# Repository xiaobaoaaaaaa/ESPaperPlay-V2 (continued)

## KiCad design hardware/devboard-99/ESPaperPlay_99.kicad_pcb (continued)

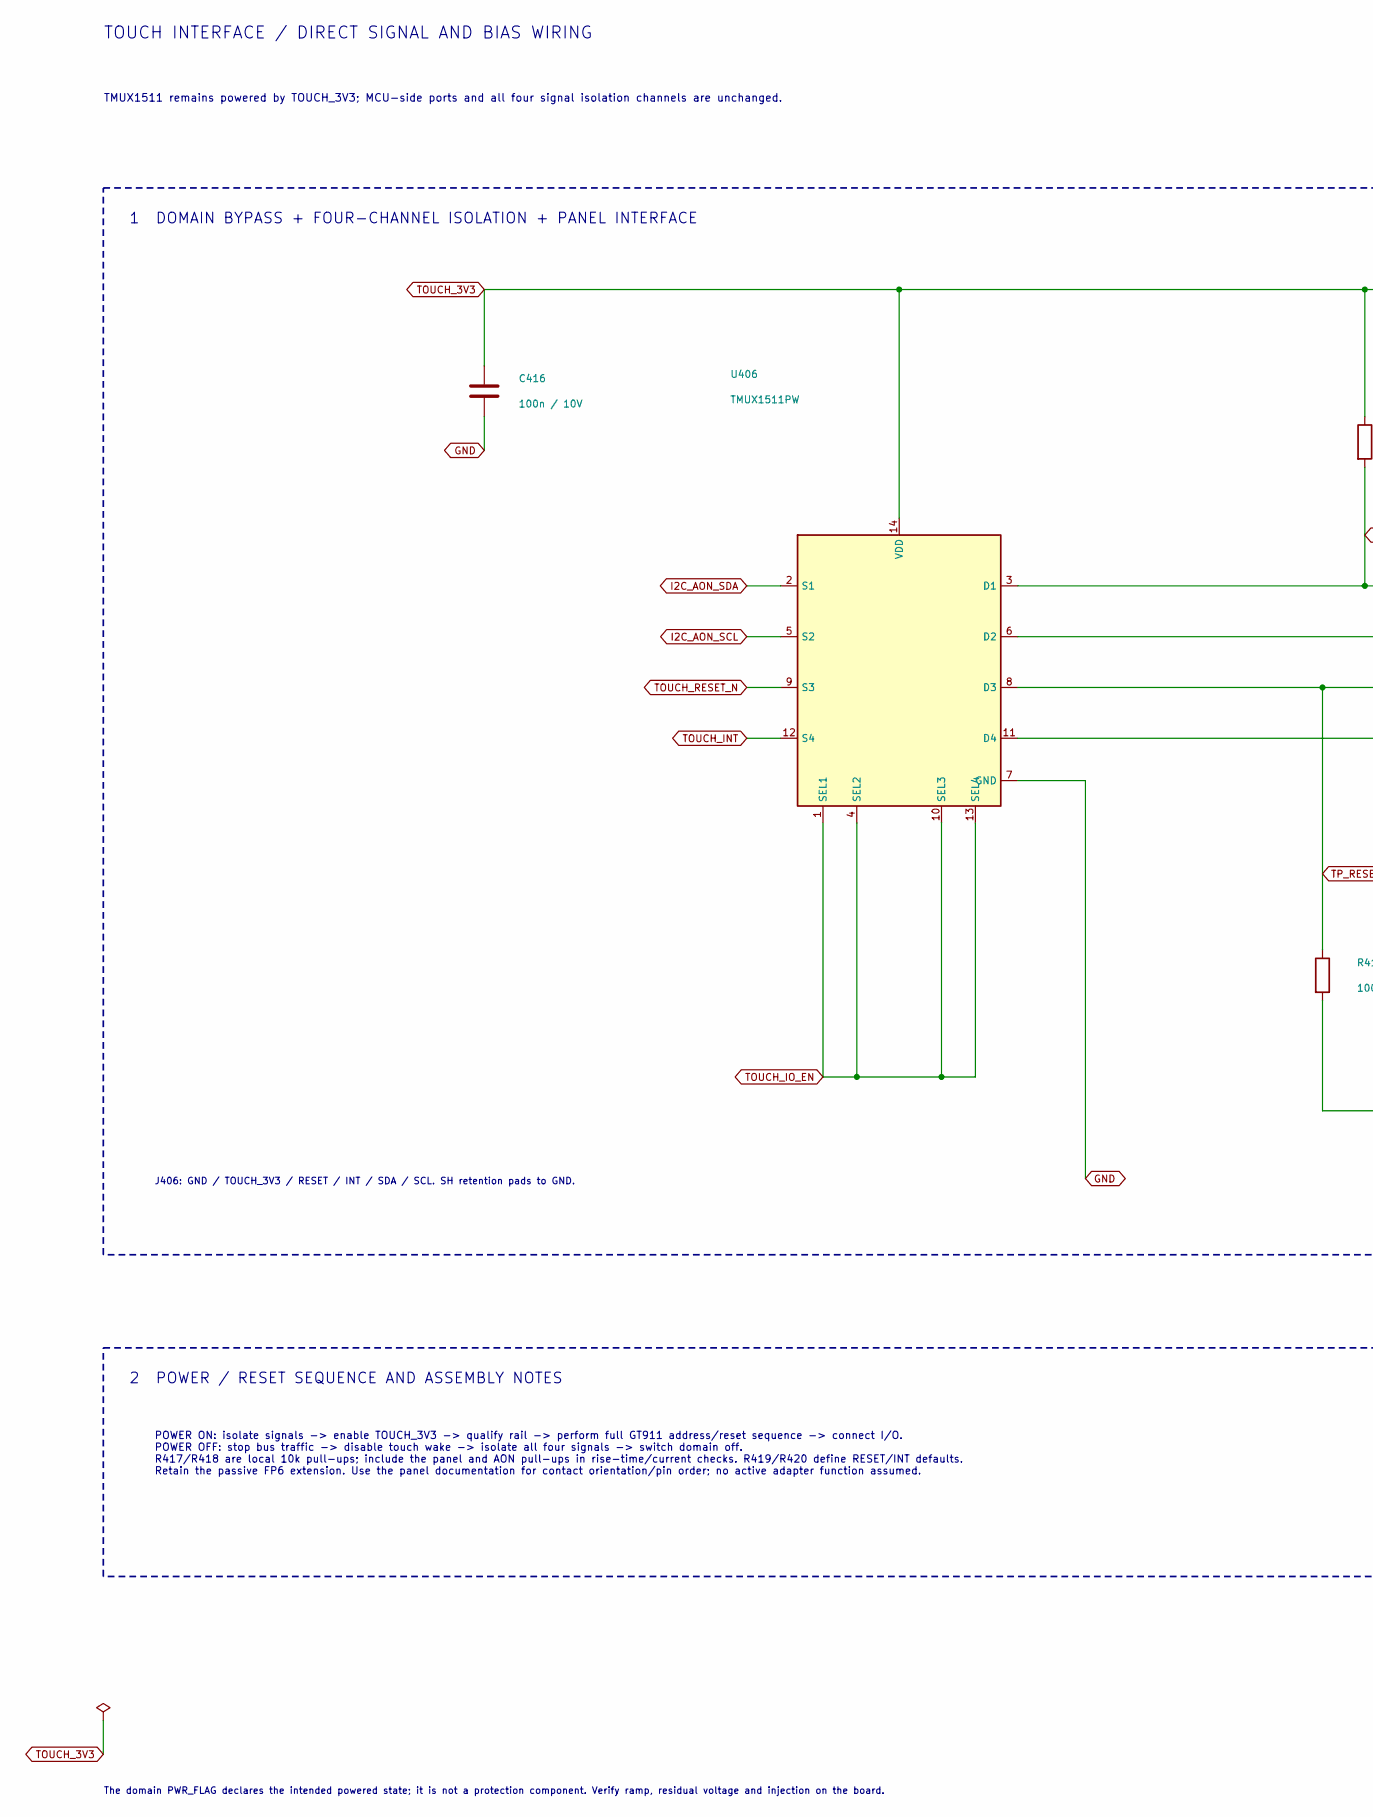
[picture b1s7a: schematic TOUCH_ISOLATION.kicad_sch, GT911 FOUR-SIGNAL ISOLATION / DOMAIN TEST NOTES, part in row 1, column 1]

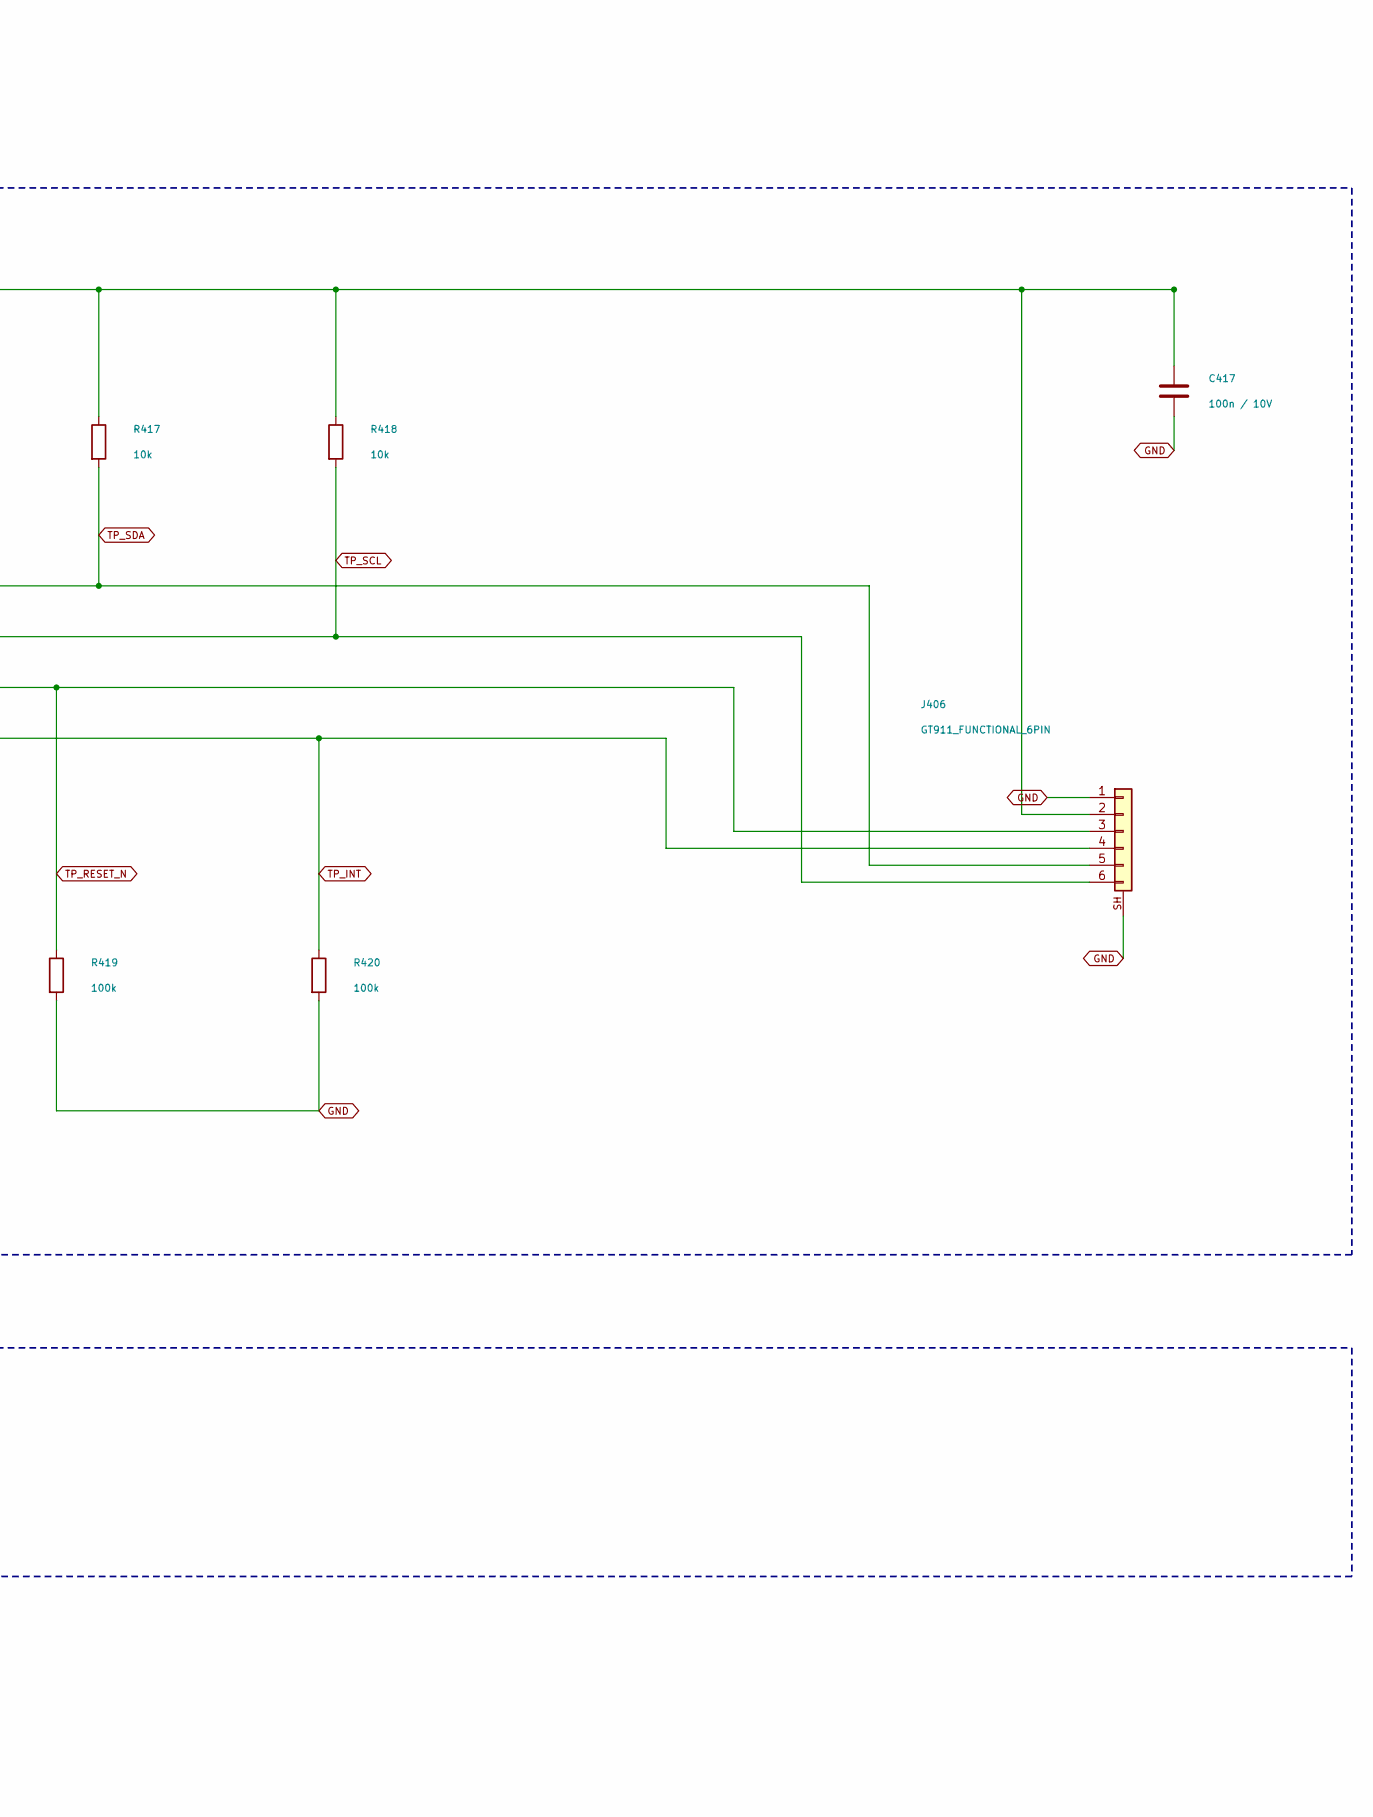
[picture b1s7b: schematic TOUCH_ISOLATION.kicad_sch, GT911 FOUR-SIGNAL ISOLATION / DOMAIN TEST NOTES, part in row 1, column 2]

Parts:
C416, C417: 100n / 10V; C_0603_1608Metric
J406: GT911_FUNCTIONAL_6PIN; LAILAN_LAIL-FPC-CDX01-6P0.5-GW_1x06_P0.50mm_SH
R417, R418: 10k; R_0603_1608Metric
R419, R420: 100k; R_0603_1608Metric
U406: TMUX1511PW; TSSOP-14_4.4x5mm_P0.65mm

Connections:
GND: C416.2, C417.2, J406.1, J406.SH, R419.2, R420.2, U406.7 (GND); also elsewhere on the board
I2C_AON_SCL: U406.5 (S2); also elsewhere on the board
I2C_AON_SDA: U406.2 (S1); also elsewhere on the board
TOUCH_3V3: C416.1, C417.1, J406.2, R417.1, R418.1, U406.14 (VDD); also elsewhere on the board
TOUCH_INT: U406.12 (S4); also elsewhere on the board
TOUCH_IO_EN: U406.1 (SEL1), U406.4 (SEL2), U406.10 (SEL3), U406.13 (SEL4); also elsewhere on the board
TOUCH_RESET_N: U406.9 (S3); also elsewhere on the board
TP_INT: J406.4, R420.1, U406.11 (D4)
TP_RESET_N: J406.3, R419.1, U406.8 (D3)
TP_SCL: J406.6, R418.2, U406.6 (D2)
TP_SDA: J406.5, R417.2, U406.3 (D1)

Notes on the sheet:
TOUCH INTERFACE / DIRECT SIGNAL AND BIAS WIRING
TMUX1511 remains powered by TOUCH_3V3; MCU-side ports and all four signal isolation channels are unchanged.
1 DOMAIN BYPASS + FOUR-CHANNEL ISOLATION + PANEL INTERFACE
J406: GND / TOUCH_3V3 / RESET / INT / SDA / SCL. SH retention pads to GND.
2 POWER / RESET SEQUENCE AND ASSEMBLY NOTES
POWER ON: isolate signals -> enable TOUCH_3V3 -> qualify rail -> perform full GT911 address/reset sequence -> connect I/O. POWER OFF: stop bus traffic -> disable touch wake -> isolate all four signals -> switch domain off. R417/R418 are local 10k pull-ups; include the panel and AON pull-ups in rise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
The domain PWR_FLAG declares the intended powered state; it is not a protection component. Verify ramp, residual voltage and injection on the board.

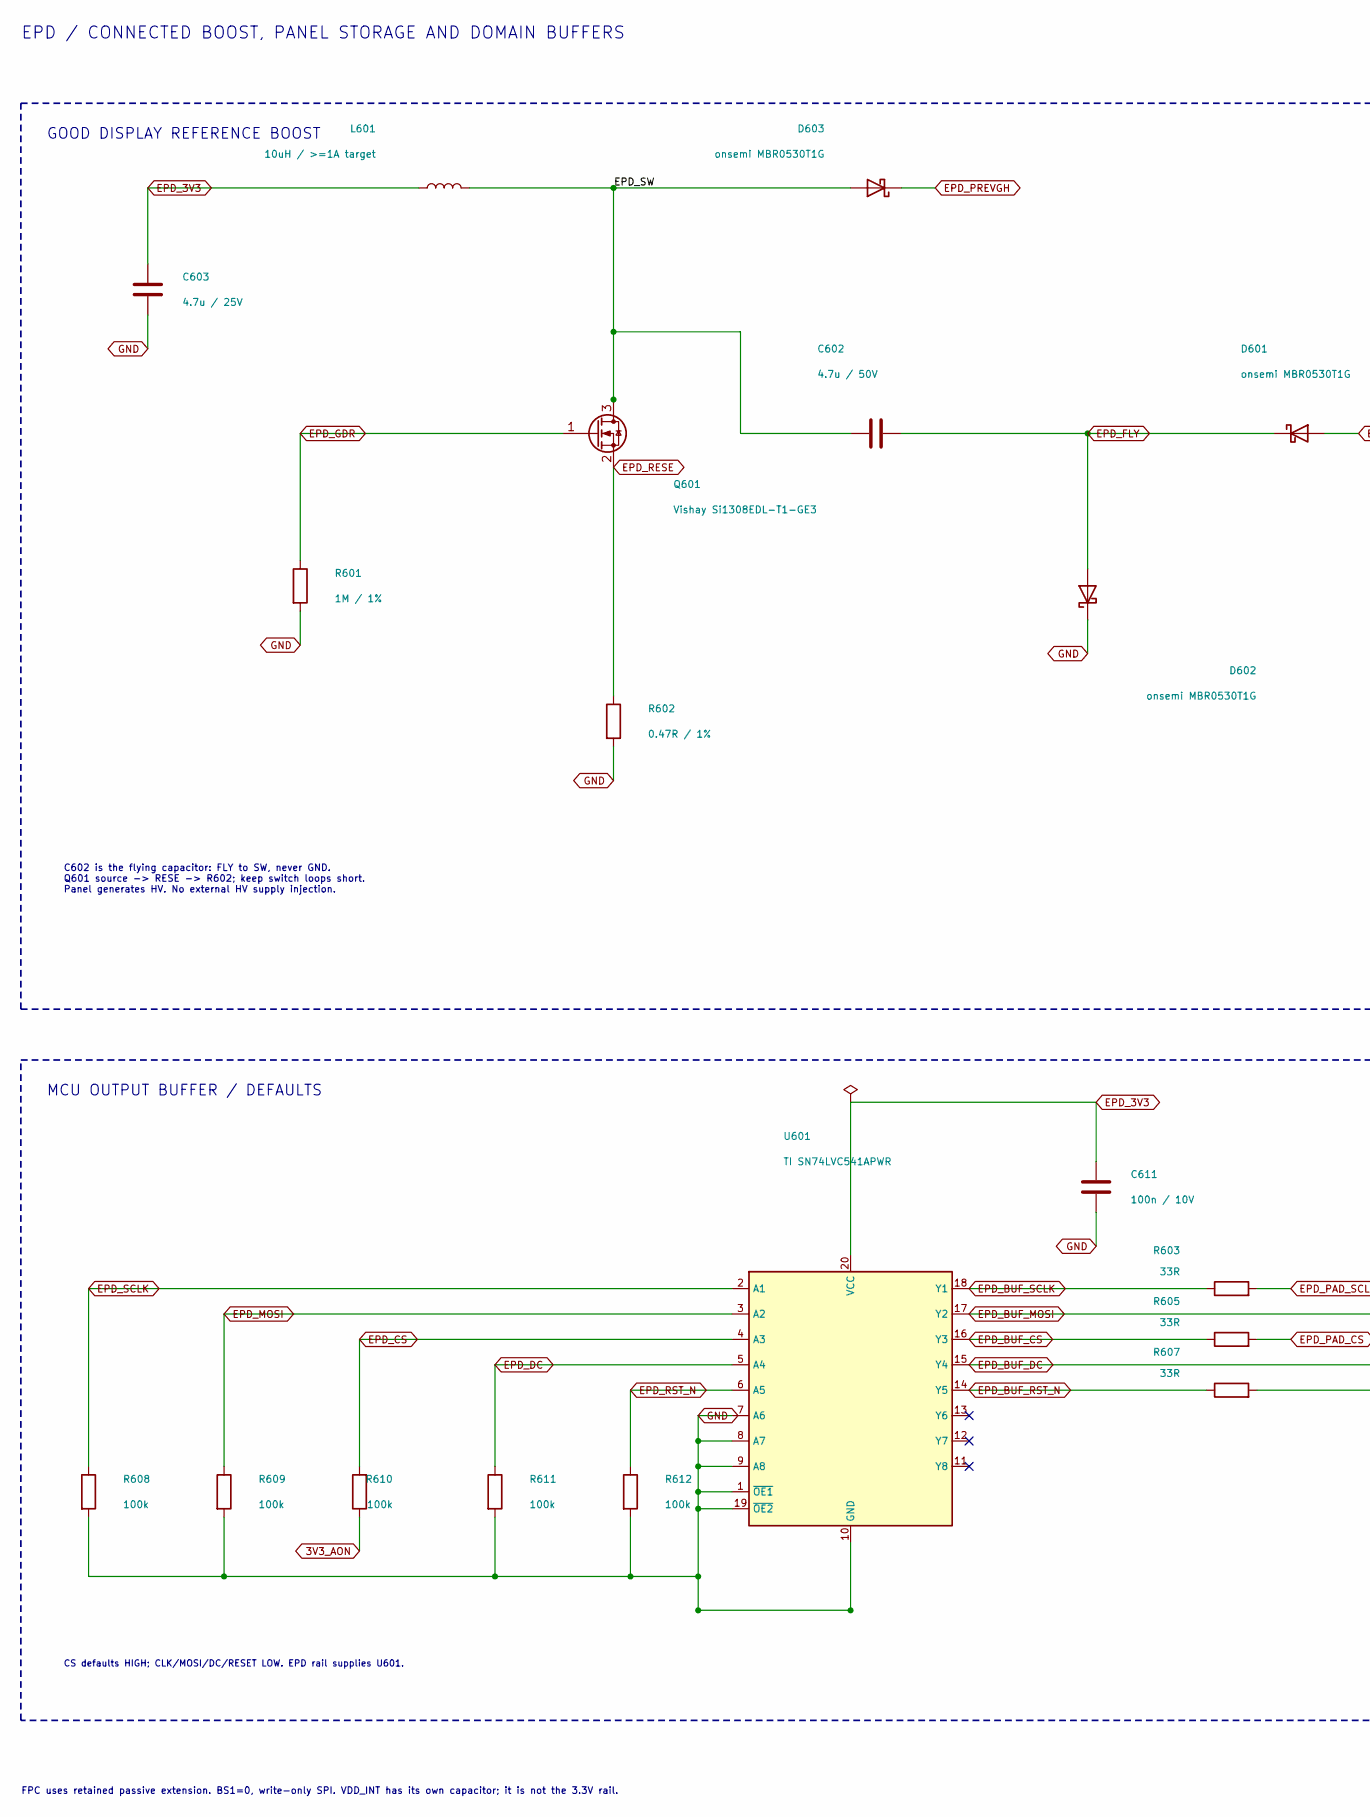
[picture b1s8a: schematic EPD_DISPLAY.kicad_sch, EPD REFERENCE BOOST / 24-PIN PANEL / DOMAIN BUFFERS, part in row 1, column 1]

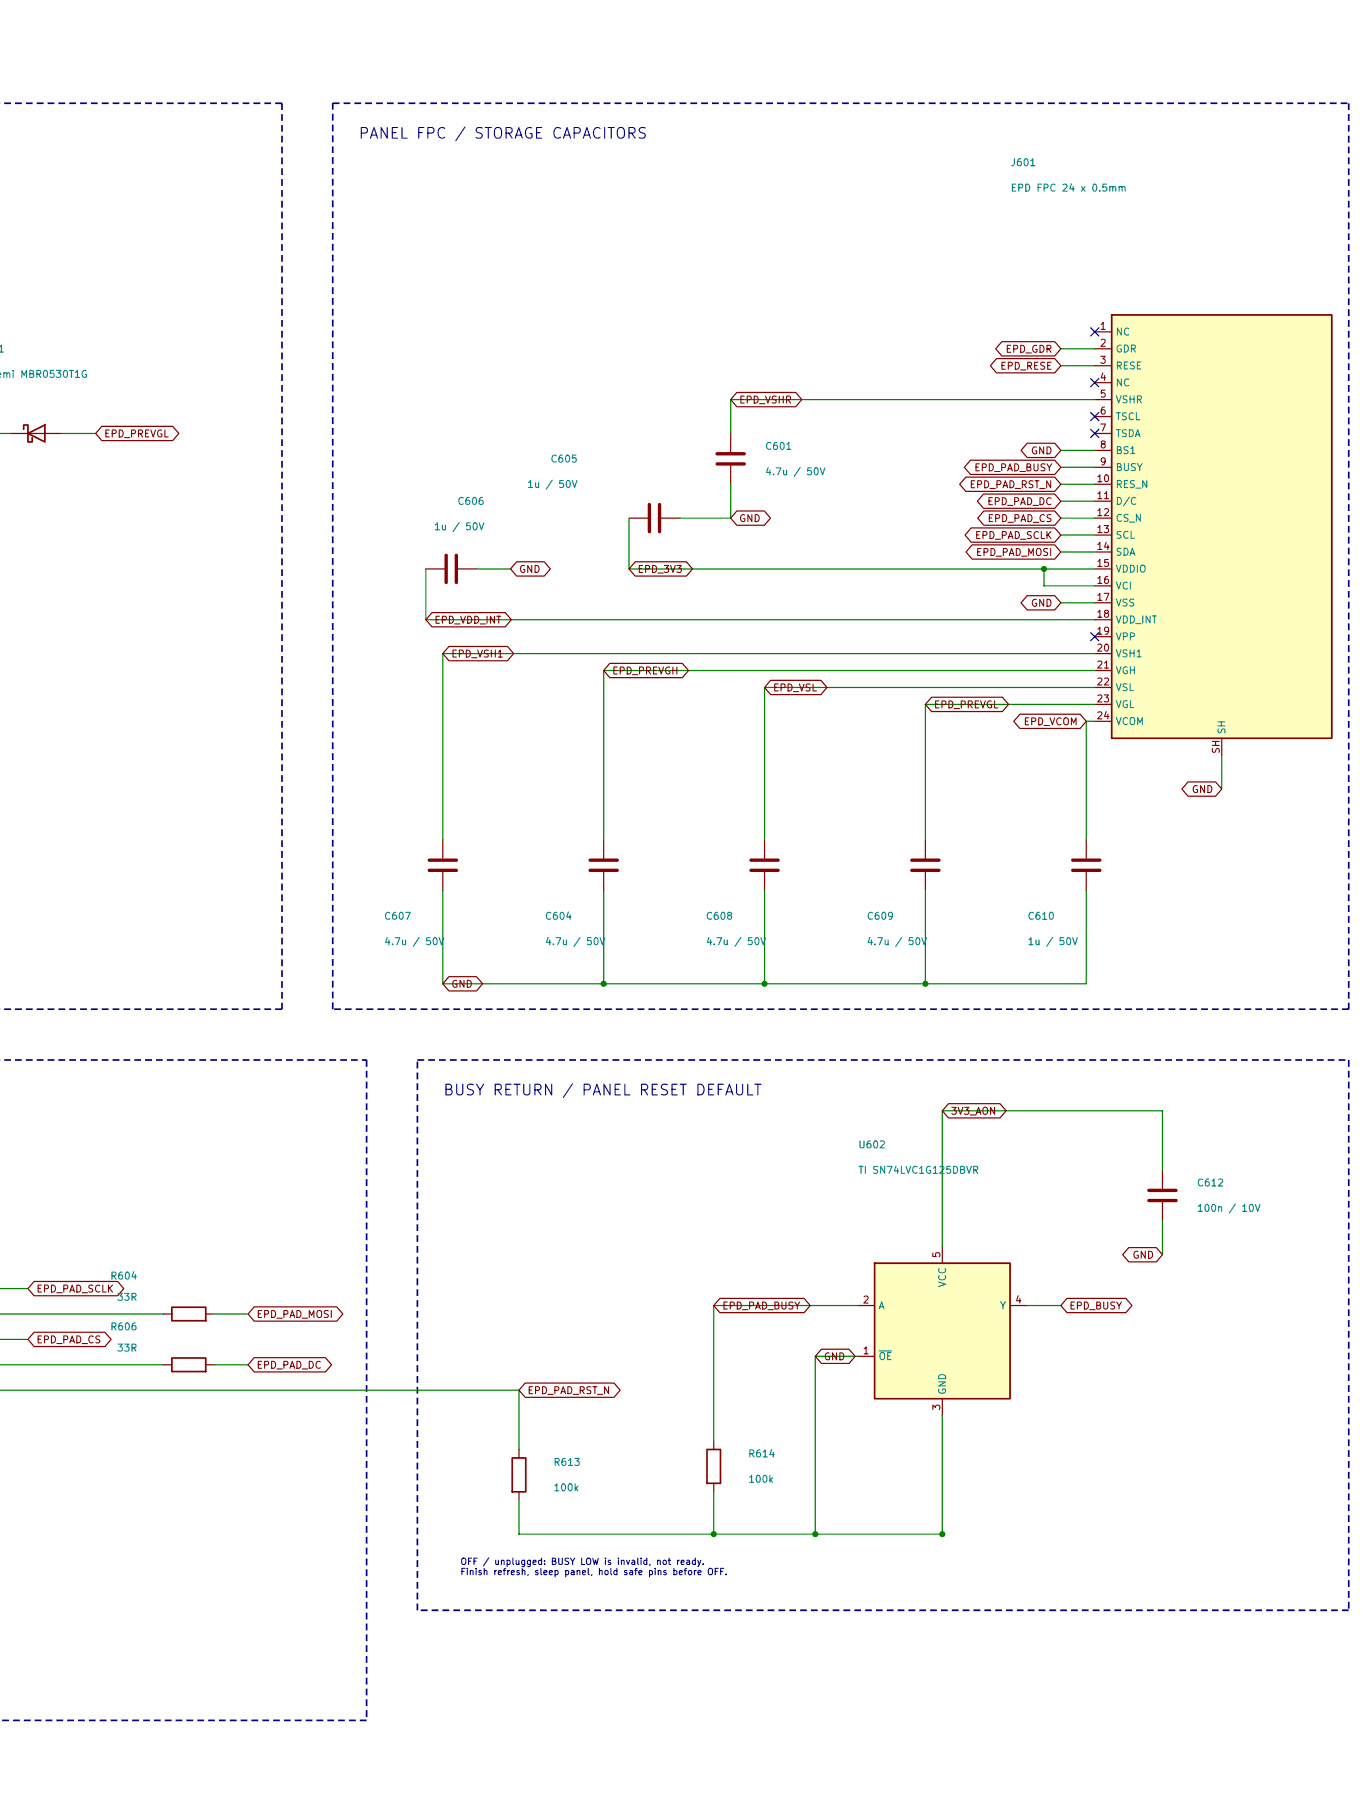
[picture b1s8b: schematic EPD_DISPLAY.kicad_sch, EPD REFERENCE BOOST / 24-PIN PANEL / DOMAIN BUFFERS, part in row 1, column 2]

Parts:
C601, C602, C604, C607, C608, C609: 4.7u / 50V; C_1206_3216Metric
C603: 4.7u / 25V; C_0805_2012Metric
C605, C606, C610: 1u / 50V; C_0805_2012Metric
C611, C612: 100n / 10V; C_0603_1608Metric
D601, D602, D603: onsemi MBR0530T1G; D_SOD-123
J601: EPD FPC 24 x 0.5mm; HOAUC_HYCW3D-05FPC24-200B_1x24_P0.50mm_SH
L601: 10uH / >=1A target; L_Bourns-SRN4018
Q601: Vishay Si1308EDL-T1-GE3; Vishay_SC70_3_AN826_72601
R601: 1M / 1%; R_0603_1608Metric
R602: 0.47R / 1%; Vishay_WFM2010_5.08x2.54mm
R603, R604, R605, R606, R607: 33R; R_0603_1608Metric
R608, R609, R610, R611, R612, R613, R614: 100k; R_0603_1608Metric
U601: TI SN74LVC541APWR; TSSOP-20_4.4x6.5mm_P0.65mm
U602: TI SN74LVC1G125DBVR; SOT-23-5

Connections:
3V3_AON: C612.1, R610.1, U602.5 (VCC); also elsewhere on the board
/EPD_DISPLAY/EPD_SW: C602.2, D603.2 (A), L601.2, Q601.3 (D)
EPD_3V3: C603.1, C605.1, C611.1, J601.15 (VDDIO), J601.16 (VCI), L601.1, U601.20 (VCC); also elsewhere on the board
EPD_BUF_CS: R605.1, U601.16 (Y3)
EPD_BUF_DC: R606.1, U601.15 (Y4)
EPD_BUF_MOSI: R604.1, U601.17 (Y2)
EPD_BUF_RST_N: R607.1, U601.14 (Y5)
EPD_BUF_SCLK: R603.1, U601.18 (Y1)
EPD_BUSY: U602.4 (Y); also elsewhere on the board
EPD_CS: R610.2, U601.4 (A3); also elsewhere on the board
EPD_DC: R611.1, U601.5 (A4); also elsewhere on the board
EPD_FLY: C602.1, D601.1 (K), D602.2 (A)
EPD_GDR: J601.2 (GDR), Q601.1 (G), R601.1
EPD_MOSI: R609.1, U601.3 (A2); also elsewhere on the board
EPD_PAD_BUSY: J601.9 (BUSY), R614.1, U602.2 (A)
EPD_PAD_CS: J601.12 (CS_N), R605.2
EPD_PAD_DC: J601.11 (D/C), R606.2
EPD_PAD_MOSI: J601.14 (SDA), R604.2
EPD_PAD_RST_N: J601.10 (RES_N), R607.2, R613.1
EPD_PAD_SCLK: J601.13 (SCL), R603.2
EPD_PREVGH: C604.1, D603.1 (K), J601.21 (VGH)
EPD_PREVGL: C609.1, D601.2 (A), J601.23 (VGL)
EPD_RESE: J601.3 (RESE), Q601.2 (S), R602.1
EPD_RST_N: R612.1, U601.6 (A5); also elsewhere on the board
EPD_SCLK: R608.1, U601.2 (A1); also elsewhere on the board
EPD_VCOM: C610.1, J601.24 (VCOM)
EPD_VDD_INT: C606.1, J601.18 (VDD_INT)
EPD_VSH1: C607.1, J601.20 (VSH1)
EPD_VSHR: C601.1, J601.5 (VSHR)
EPD_VSL: C608.1, J601.22 (VSL)
GND: C601.2, C603.2, C604.2, C605.2, C606.2, C607.2, C608.2, C609.2, C610.2, C611.2, C612.2, D602.1 (K), J601.8 (BS1), J601.17 (VSS), J601.SH, R601.2, R602.2, R608.2, R609.2, R611.2, R612.2, R613.2, R614.2, U601.1 (~OE1), U601.7 (A6), U601.8 (A7), U601.9 (A8), U601.10 (GND), U601.19 (~OE2), U602.1 (~OE), U602.3 (GND); also elsewhere on the board

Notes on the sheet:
EPD / CONNECTED BOOST, PANEL STORAGE AND DOMAIN BUFFERS
GOOD DISPLAY REFERENCE BOOST
PANEL FPC / STORAGE CAPACITORS
MCU OUTPUT BUFFER / DEFAULTS
BUSY RETURN / PANEL RESET DEFAULT
C602 is the flying capacitor: FLY to SW, never GND. Q601 source -> RESE -> R602; keep switch loops short. Panel generates HV. No external HV supply injection.
CS defaults HIGH; CLK/MOSI/DC/RESET LOW. EPD rail supplies U601.
OFF / unplugged: BUSY LOW is invalid, not ready. Finish refresh, sleep panel, hold safe pins before OFF.
FPC uses retained passive extension. BS1=0, write-only SPI. VDD_INT has its own capacitor; it is not the 3.3V rail.

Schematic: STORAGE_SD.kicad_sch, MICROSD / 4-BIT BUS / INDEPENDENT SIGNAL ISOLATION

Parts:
C701, C703, C705: 100n / 10V; C_0603_1608Metric
C702: 10u / 10V; C_0805_2012Metric
C704: 10n / 50V; C_0603_1608Metric
J701: Hirose DM3AT-SF-PEJM5; microSD_HC_Hirose_DM3AT-SF-PEJM5
R701, R702, R703, R704, R705: 10k / 1%; R_0603_1608Metric
R706: 100k; R_0603_1608Metric
R708: 100R; R_0603_1608Metric
R710: 22R; R_0603_1608Metric
R711, R712, R713, R714, R715: 0R; R_0603_1608Metric
U701, U706: TI TMUX1511PW; TSSOP-14_4.4x5mm_P0.65mm
U702, U703, U704, U705: TI TPD2E2U06DCKR; TI_DCK0003A_SC70_3_Recommended

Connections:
/STORAGE_SD/SD_CLK_BUS: R710.2, U701.2 (S1)
/STORAGE_SD/SD_CMD_BUS: R711.2, U701.5 (S2)
/STORAGE_SD/SD_D0_BUS: R712.2, U701.9 (S3)
/STORAGE_SD/SD_D1_BUS: R713.2, U701.12 (S4)
/STORAGE_SD/SD_D2_BUS: R714.2, U706.2 (S1)
/STORAGE_SD/SD_D3_BUS: R715.2, U706.5 (S2)
GND: C701.2, C702.2, C703.2, C704.2, C705.2, J701.6 (VSS), J701.10 (DET_A), J701.SH (SHIELD), R706.2, U701.7 (GND), U702.3, U703.3, U704.3, U705.3, U706.7 (GND), U706.10 (SEL3), U706.13 (SEL4); also elsewhere on the board
SD_3V3: C701.1, C702.1, C703.1, C705.1, J701.4 (VDD), R701.1, R702.1, R703.1, R704.1, R705.1, U701.14 (VDD), U705.2, U706.14 (VDD); also elsewhere on the board
SD_CARD_CLK: J701.5 (CLK), R706.1, U701.3 (D1), U702.1
SD_CARD_CMD: J701.3 (CMD), R701.2, U701.6 (D2), U702.2
SD_CARD_D0: J701.7 (DAT0), R702.2, U701.8 (D3), U703.1
SD_CARD_D1: J701.8 (DAT1), R703.2, U701.11 (D4), U703.2
SD_CARD_D2: J701.1 (DAT2), R704.2, U704.1, U706.3 (D1)
SD_CARD_D3: J701.2 (DAT3/CD), R705.2, U704.2, U706.6 (D2)
SD_CD_N: C704.1, R708.1; also elsewhere on the board
SD_CLK: R710.1; also elsewhere on the board
SD_CMD: R711.1; also elsewhere on the board
SD_D0: R712.1; also elsewhere on the board
SD_D1: R713.1; also elsewhere on the board
SD_D2: R714.1; also elsewhere on the board
SD_D3: R715.1; also elsewhere on the board
SD_DETECT_CONTACT: J701.9 (DET_B), R708.2, U705.1
SD_IO_EN: U701.1 (SEL1), U701.4 (SEL2), U701.10 (SEL3), U701.13 (SEL4), U706.1 (SEL1), U706.4 (SEL2); also elsewhere on the board

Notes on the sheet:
MICROSD / WIRED ISOLATION, PULL-UPS AND CARD DETECT
CLK / CMD / D0 / D1
D2 / D3
CARD SOCKET / PULL-UPS / DETECT / ESD
All SEL -> SD_IO_EN (IOX P13). R223 default pull-down is on control page.
Spare channels: SEL LOW, S/D NC.
Five pull-ups use SD_3V3; CLK is pulled LOW. Card power and SD_IO_EN are independently controlled.
DAT3 is not the mechanical detect contact. R708/C704 filter contact bounce; firmware still debounces.
Parallel ESD clamps at the connector; short return to GND.
ON: isolate -> power valid -> connect I/O -> initialize. OFF: flush/unmount -> isolate -> power OFF. No UHS 1.8V; begin at 400kHz init, then 4-bit 20MHz target. Values and connectivity unchanged from r5.

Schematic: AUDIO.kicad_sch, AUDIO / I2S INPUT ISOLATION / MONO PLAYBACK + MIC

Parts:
C801, C802, C804, C806, C808: 100n / 10V; C_0603_1608Metric
C803: 10u / 10V; C_0805_2012Metric
C805: 1u / 16V; C_0603_1608Metric
J801: SPEAKER / 8R CANDIDATE; PhoenixContact_MKDS-1-2-3.5_1751248_1x02_P3.50mm_Horizontal
R802, R803, R804, R805, R813: 100k; R_0603_1608Metric
R806: 2.00k / 1%; R_0603_1608Metric
R808, R809, R810: 22R; R_0603_1608Metric
R811: 0R / SPK_P; R_0805_2012Metric
R812: 0R / SPK_N; R_0805_2012Metric
U801: Nexperia 74LVC125APW; TSSOP-14_4.4x5mm_P0.65mm
U802: MAX98357AETE+T; Analog_MAX98357A_T1633-4_3x3mm_P0.5mm_EP1.23mm
U803: DMM-4026-B-I2S-R; PUI_DMM_4026_B_I2S_R_7Pad_NPTH0.60
U804: TI SN74LVC1G125DBVR; SOT-23-5
U805: TI SN74LVC1G14DBVR; SOT-23-5

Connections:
3V3_AON: C808.1, U804.5 (VCC); also elsewhere on the board
/AUDIO/AMP_OUTN: R812.1, U802.10 (OUTN)
/AUDIO/AMP_OUTP: R811.1, U802.9 (OUTP)
/AUDIO/AMP_SD_MODE: R805.1, R806.2, U802.4 (~SD_MODE)
/AUDIO/AUDIO_BCLK_BUF: R808.1, U801.3 (1Y)
/AUDIO/AUDIO_DIN_BUF: R810.1, U801.8 (3Y)
/AUDIO/AUDIO_OE_N: U801.1 (~1OE), U801.4 (~2OE), U801.10 (~3OE), U801.13 (~4OE), U805.4 (Y_INV)
/AUDIO/AUDIO_SD_BUF: R806.1, U801.11 (4Y)
/AUDIO/AUDIO_WS_BUF: R809.1, U801.6 (2Y)
/AUDIO/I2S_BCLK_AUDIO: R802.1, R808.2, U802.16 (BCLK), U803.6 (SCK)
/AUDIO/I2S_DIN_AUDIO: R804.1, R810.2, U802.1 (DIN)
/AUDIO/I2S_WS_AUDIO: R803.1, R809.2, U802.14 (LRCLK), U803.5 (WS)
/AUDIO/MIC_SD_RAW: R813.1, U803.7 (SD), U804.2 (A)
/AUDIO/SPK_N: J801.2, R812.2
/AUDIO/SPK_P: J801.1, R811.2
AMP_SHUTDOWN: U801.12 (4A); also elsewhere on the board
AMP_SYS: C802.1, C803.1, U802.2 (GAIN_SLOT), U802.7 (VDD), U802.8 (VDD); also elsewhere on the board
AUDIO_EN: U805.2 (A_ST); also elsewhere on the board
GND: C801.2, C802.2, C803.2, C804.2, C805.2, C806.2, C808.2, R802.2, R803.2, R804.2, R805.2, R813.2, U801.7 (GND), U802.3 (GND), U802.11 (GND), U802.15 (GND), U802.17 (PAD), U803.1 (LR), U803.2 (CONFIG), U803.4 (GND), U804.1 (~OE), U804.3 (GND), U805.3 (GND); also elsewhere on the board
I2S_BCLK: U801.2 (1A); also elsewhere on the board
I2S_WS: U801.5 (2A); also elsewhere on the board
MIC_3V3: C801.1, C804.1, C805.1, C806.1, U801.14 (VCC), U803.3 (VDD), U805.5 (VCC); also elsewhere on the board
MIC_DATA: U804.4 (Y); also elsewhere on the board
SPEAKER_DATA: U801.9 (3A); also elsewhere on the board

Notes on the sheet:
AUDIO / CONNECTED FUNCTIONAL MODULES
OUTPUT ISOLATION + ENABLE
MONO AMPLIFIER + BTL SPEAKER
MICROPHONE + DATA RETURN
OPERATING NOTES
AUDIO_EN drives all four /OE pins. U801/U805 powered from MIC_3V3; exact Ioff-rated vendor.
8 ohm / 2W selected speaker. Both BTL wires float. 6dB gain; playback in LEFT slot; initial output cap 0.5W.
LR and CONFIG strapped LOW. SD pull-down before AON return buffer.
48kHz / 2 x 32-bit I2S slots / 64fs. Mute -> enable rails -> clocks/zero data -> discard startup frames -> unmute. OFF: mute, finish audio, stop clocks, drive safe levels, then AUDIO_EN=0. Verify low-battery THD, pop, rail decay, SD_MODE injection and acoustic port. No 5V audio boost; no new firmwa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

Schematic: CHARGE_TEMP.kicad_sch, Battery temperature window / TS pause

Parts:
C901: 100n / 50V; C_0603_1608Metric
C902, C903, C904: 10n / 50V; C_0603_1608Metric
R901: 47k / 1%; R_0603_1608Metric
R902, R904: 100k / 1%; R_0603_1608Metric
R903: 12k / 1%; R_0603_1608Metric
R905: 33k / 1%; R_0603_1608Metric
R906: 10k / 1%; R_0603_1608Metric
R907, R908: 330k / 1%; R_0603_1608Metric
U901: TLV1822DR; TI_D0008A_SOIC8

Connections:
/CHARGE_TEMP/NTC_COLD_REF: C904.1, R904.2, R905.1, R908.2, U901.5 (COLD_IN+)
/CHARGE_TEMP/NTC_HOT_REF: C903.1, R902.2, R903.1, U901.2 (HOT_IN-)
BAT_NTC: C902.1, R901.2, R907.2, U901.3 (HOT_IN+), U901.6 (COLD_IN-); also elsewhere on the board
CHG_TS: R906.1, R907.1, R908.1, U901.1 (HOT_OUT), U901.7 (COLD_OUT); also elsewhere on the board
GND: C901.2, C902.2, C903.2, C904.2, R903.2, R905.2, R906.2, U901.4 (V-); also elsewhere on the board
VIN_5V: C901.1, R901.1, R902.1, R904.1, U901.8 (V+); also elsewhere on the board

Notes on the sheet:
CHARGE TEMPERATURE WINDOW / CONNECTED ANALOG CIRCUIT
Assumed Honeywell175-103LAE-301 Rev.B curve; actual pack NTC identity remains unverified. No electrical change from r5.
1 NTC SENSE / COLD AND HOT REFERENCES / OPEN-DRAIN WINDOW
330k feedback paths produce hysteresis; solve the three coupled nodes, not separate unloaded dividers.
5V nominal pause points: cold14.8C / hot40.1C. Resume example15.5C /39.5C assumes fault TS=0.1V. NTC open -> cold fault; short -> hot fault. Either output pulls TS low, pausing charge and its timer. U901 uses the same VIN as BQ24074. No battery-only divider load; independent comparator failure is n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

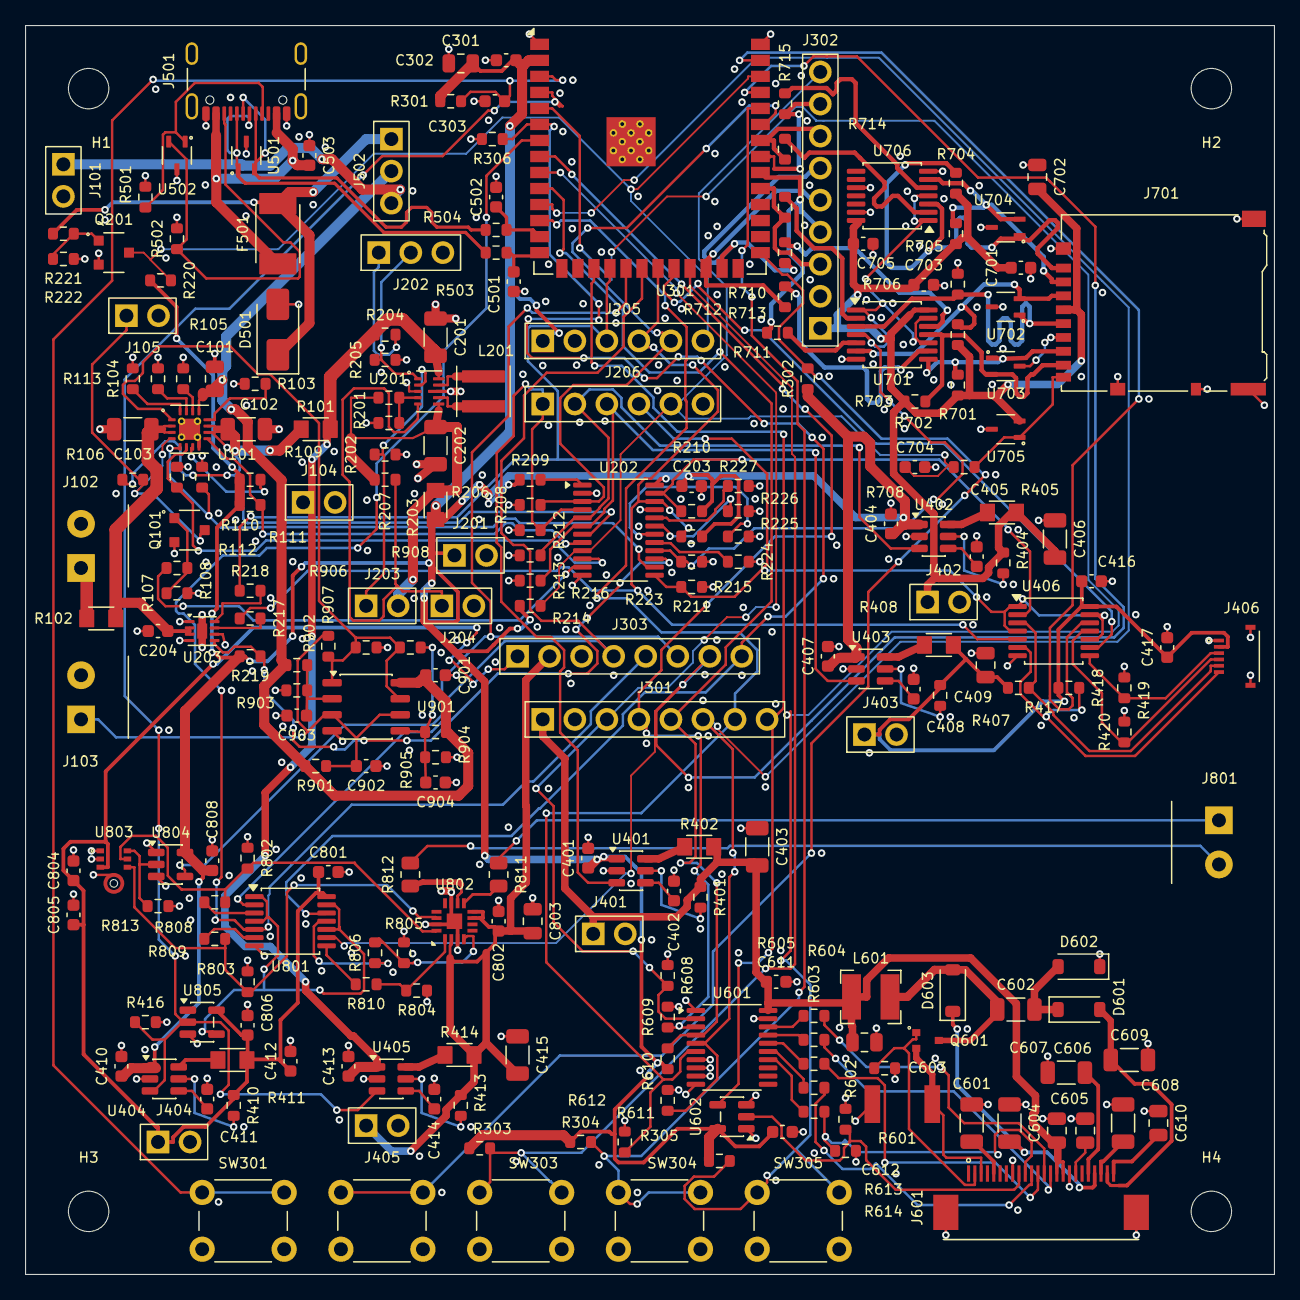
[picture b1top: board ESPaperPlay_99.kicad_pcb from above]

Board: 4 copper layers, 99.0 x 99.0 mm, 240 parts (0 on the bottom side), 156 nets.

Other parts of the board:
H1, H2, H3, H4: M3 NPTH; MountingHole_3.2mm_M3

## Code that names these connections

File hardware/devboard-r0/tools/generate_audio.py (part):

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    connect(s,'U801',{'14':'MIC_3V3','7':'GND','2':'I2S_BCLK','3':'AUDIO_BCLK_BUF',
        '5':'I2S_WS','6':'AUDIO_WS_BUF','9':'SPEAKER_DATA','8':'AUDIO_DIN_BUF',
        '12':'AMP_SHUTDOWN','11':'AUDIO_SD_BUF','1':False,'4':False,'10':False,'13':False})
    s.join_pins('U801',['1','4','10','13'],'AUDIO_OE_N',1,4)
    for pin in ['4','10']:
        x,y,_=s.components['U801'][pin]
        s.parts.append(f'(junction (at {h.n(x)} {h.n(y+h.mm(4))}) (diameter 0) '
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        passive(s,'R',ref,'22R',134,y,a,b,angle=90,
            note='Initial damping value, place close to U801 output. Validate edges and total I2S setup/hold.')
    s.comp('ESPaperPlay:SN74LVC1G14DBV_AUDIO','U805','TI SN74LVC1G14DBVR',42,105,
        prop_pos=(42,85,42,88),note='Schmitt inverter with Ioff. AUDIO_EN LOW actively raises all four OE pins before normal MIC rail decay. R416 already defaults GPIO4 LOW. Active edge avoids a 100k pull-up violating U801 input slew constraints.')
    connect(s,'U805',{'1':None,'2':'AUDIO_EN','3':'GND','4':'AUDIO_OE_N','5':'MIC_3V3'})
    passive(s,'C','C806','100n / 10V',91,106,'MIC_3V3','GND',
        note='U805 local decoupling; same switched rail as U801.')
    passive(s,'C','C801','100n / 10V',134,106,'MIC_3V3','GND',note='Place at U801 supply pins, not at remote power switch.')
    s.text('AUDIO_EN=0: U805 actively disables all outputs while MIC rail is valid.\nAt VCC=0, use the selected vendor Ioff specification; not zero leakage.\nR306 already pulls MCU AMP_SHUTDOWN low; R416 pulls AUDIO_EN low.',14,121,1.0)

    s.section('2  MAX98357A / SYS SUPPLY / LEFT CHANNEL / 6dB',175,14)
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    passive(s,'C','C802','100n / 10V',186,44,'AMP_SYS','GND',note='Place immediately at VDD7/8.')
    passive(s,'C','C803','10u / 10V',302,108,'AMP_SYS','GND',
        footprint='Capacitor_SMD:C_0805_2012Metric',note='Local bulk in addition to C415=22u at switch; use effective capacitance for startup/inrush tests.')
    passive(s,'R','R806','2.00k / 1%',224,87,'AUDIO_SD_BUF','AMP_SD_MODE',angle=90,
        note='ADI-recommended current limiting when 3.3V I/O exceeds low VDD; this is NOT complete power-off isolation.')
    for ref,net,x in [('R802','I2S_BCLK_AUDIO',180),('R803','I2S_WS_AUDIO',211),('R804','I2S_DIN_AUDIO',242),('R805','AMP_SD_MODE',273)]:
        passive(s,'R',ref,'100k',x,112,net,'GND',note='Load-side default low when U801 disabled. SD_MODE has an additional internal approximately 100k pull-down.')
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    s.comp('ESPaperPlay:DMM-4026-B-I2S-R','U803','DMM-4026-B-I2S-R',64,173,
        prop_pos=(64,145,64,148),note='PUI public catalogue candidate; lifecycle/supply to confirm before BOM freeze. Exact 7-pad footprint/acoustic hole pending. LR=LOW selects LEFT; CONFIG=LOW required at power-up.')
    connect(s,'U803',{'1':'GND','2':'GND','3':'MIC_3V3','4':'GND','5':'I2S_WS_AUDIO','6':'I2S_BCLK_AUDIO','7':'MIC_SD_RAW'})
    passive(s,'C','C804','100n / 10V',20,169,'MIC_3V3','GND',note='PUI pin table requires local 0.1uF at VDD3.')
    passive(s,'C','C805','1u / 10V',20,200,'MIC_3V3','GND',note='Local bulk candidate; review Wi-Fi/EPD noise and power-ramp behavior.')
    s.comp('ESPaperPlay:SN74LVC1G125DBV_AUDIO','U804','TI SN74LVC1G125DBVR',128,172,
        prop_pos=(128,151,128,154),note='AON-powered return buffer, overvoltage-tolerant input and explicit Ioff at VCC=0. Prevent direct MIC residual supply injection into an unpowered MCU input.')
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
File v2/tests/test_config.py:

#!/usr/bin/env python3
"""Reject configuration errors which could select unavailable pins or break OTA."""
import copy
import json
from pathlib import Path
import sys
import tempfile
import unittest

ROOT = Path(__file__).resolve().parents[1]
sys.path.insert(0, str(ROOT / "tools"))
from check_board import validate
from check_layout import validate_layout


class BoardTests(unittest.TestCase):
    def setUp(self):
        self.profile = json.loads((ROOT / "boards/legacy_n16r8.json").read_text())

    def test_forbidden_memory_pins(self):
        for gpio in (26, 34, 35, 36, 37):
            with self.subTest(gpio=gpio):
                candidate = copy.deepcopy(self.profile)
                candidate["pins"]["epd_sclk"] = gpio
                with self.assertRaises(ValueError):
                    validate(candidate)

    def test_duplicate_pin(self):
        self.profile["pins"]["sd_clk"] = self.profile["pins"]["epd_sclk"]
        with self.assertRaises(ValueError):
            validate(self.profile)

    def test_usb_repurposed(self):
        self.profile["pins"].pop("usb_dm")
        self.profile["pins"]["new_power_enable"] = 19
        with self.assertRaises(ValueError):
            validate(self.profile)

    def test_unreviewed_strap(self):
        self.profile["pins"]["epd_sclk"] = 45
        with self.assertRaises(ValueError):
            validate(self.profile)

    def test_input_only_gpio_as_output(self):
        self.profile["pins"]["epd_sclk"] = 46
        self.profile["acknowledged_strapping_roles"].append("epd_sclk")
        with self.assertRaises(ValueError):
            validate(self.profile)

    def test_four_bit_without_all_lanes(self):
        self.profile["sd_bus_width"] = 4
        del self.profile["pins"]["sd_d3"]
        with self.assertRaises(ValueError):
            validate(self.profile)

    def test_sd_required_signals_in_each_mode(self):
        for width in (1, 4):
            for signal in ("sd_clk", "sd_cmd", "sd_d0"):
                with self.subTest(width=width, signal=signal):
                    profile = copy.deepcopy(self.profile)
                    profile["sd_bus_width"] = width
                    del profile["pins"][signal]
                    with self.assertRaises(ValueError):
                        validate(profile)

    def test_profile_shape(self):
        with self.assertRaises(ValueError):
            validate([])
        self.profile["sd_bus_width"] = True
        with self.assertRaises(ValueError):
            validate(self.profile)

    def test_memory_upgrade_not_silent(self):
        self.profile["psram_bytes"] *= 2
        with self.assertRaises(ValueError):
            validate(self.profile)


class PartitionTests(unittest.TestCase):
    def assert_bad(self, old, new):
        content = (ROOT / "partitions.csv").read_text()
        self.assertIn(old, content)
        with tempfile.TemporaryDirectory() as directory:
            path = Path(directory) / "partitions.csv"
            path.write_text(content.replace(old, new))
            with self.assertRaises(ValueError):
                validate_layout(path)

    def test_overlap(self):
        self.assert_bad("0x520000", "0x510000")

    def test_flash_overflow(self):
        self.assert_bad("0x1e0000", "0x2e0000")

    def test_missing_slot(self):
        self.assert_bad("ota_1,   app,  ota_1", "other,   app,  test")

    def test_invalid_ota_metadata(self):
        self.assert_bad("0xf000,   0x2000", "0xf000,   0x1000")


if __name__ == "__main__":
    unittest.main()
